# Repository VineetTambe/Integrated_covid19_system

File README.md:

# Integrated_covid19_system
Initially, a real-time camera feed is taken and the image-processing and detection using OpenCV.
1. The barcode is detected and decoded using a camera.    
2. The same camera is used to detect if the person is wearing a mask or not. This is done with the help of image processing and haar-cascade to give efficient and real-time output. The system also ensures whether a person is wearing a mask or not and it captures a photo and maintains a database of the violators.    
3. An infrared temperature sensor is then used to monitor the temperature of the person without any contact and maps it to the corresponding barcode which was read. The system also gives an alert when the temperature crosses a certain threshold.    

Further, all the data is stored in the cloud where the analysis of every individual is carried out to understand the temperature and other patterns.    

The unit also houses a touchless sanitizer dispenser which can be activated by hovering the hand below it.    

The dashboard application is a "one-stop-shop" for the management authorities to monitor the system and gain insight

[Click here for the demo](https://youtu.be/hhcx9HmFBgw)

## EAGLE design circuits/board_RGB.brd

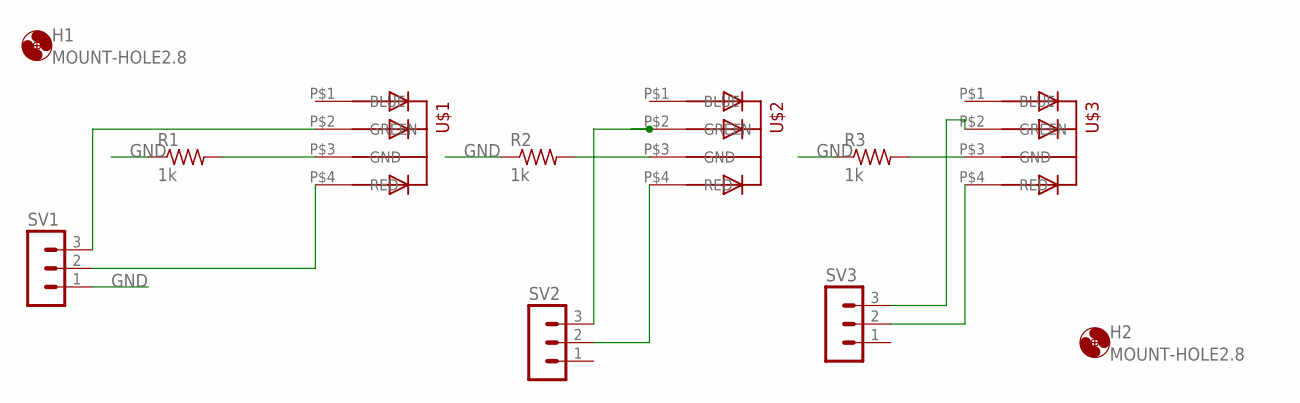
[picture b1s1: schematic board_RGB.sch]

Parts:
H1, H2: MOUNT-HOLE2.8; 2,8
R1, R2, R3: 1k; 0207/10
SV1, SV2, SV3: MA03-1
U$1, U$2, U$3: 5MMRGBLED; LED5MMRGB

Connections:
GND: R1.1, R2.1, R3.1, SV1.1
unnamed: SV2.2, U$2.P$4 (RED)
unnamed: R1.2, U$1.P$3 (GND)
unnamed: SV1.3, U$1.P$2 (GREEN)
unnamed: SV3.2, U$3.P$4 (RED)
unnamed: SV3.3, U$3.P$2 (GREEN)
unnamed: R3.2, U$3.P$3 (GND)
unnamed: R2.2, U$2.P$3 (GND)
unnamed: SV1.2, U$1.P$4 (RED)
unnamed: SV2.3, U$2.P$2 (GREEN)

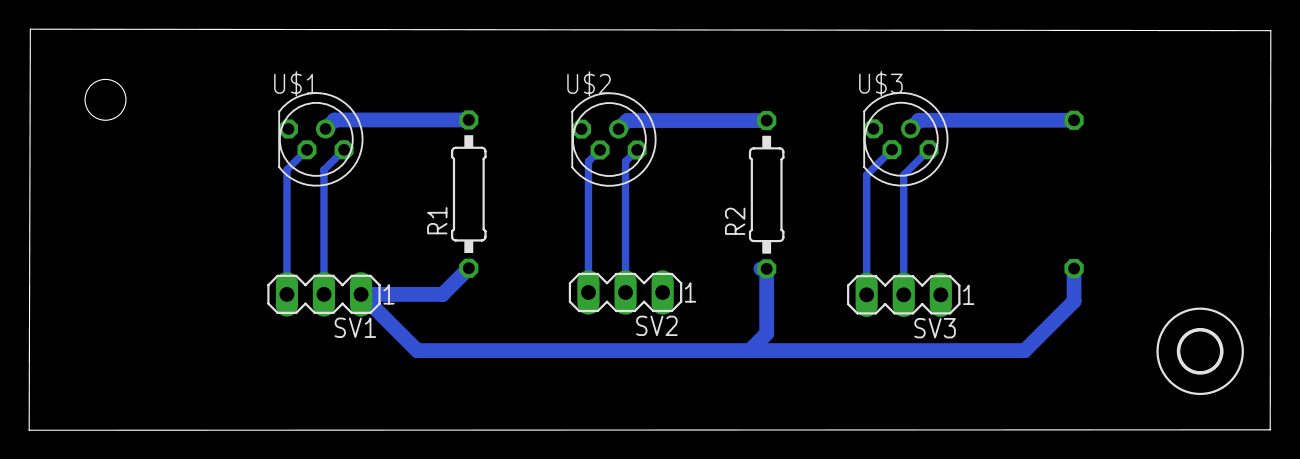
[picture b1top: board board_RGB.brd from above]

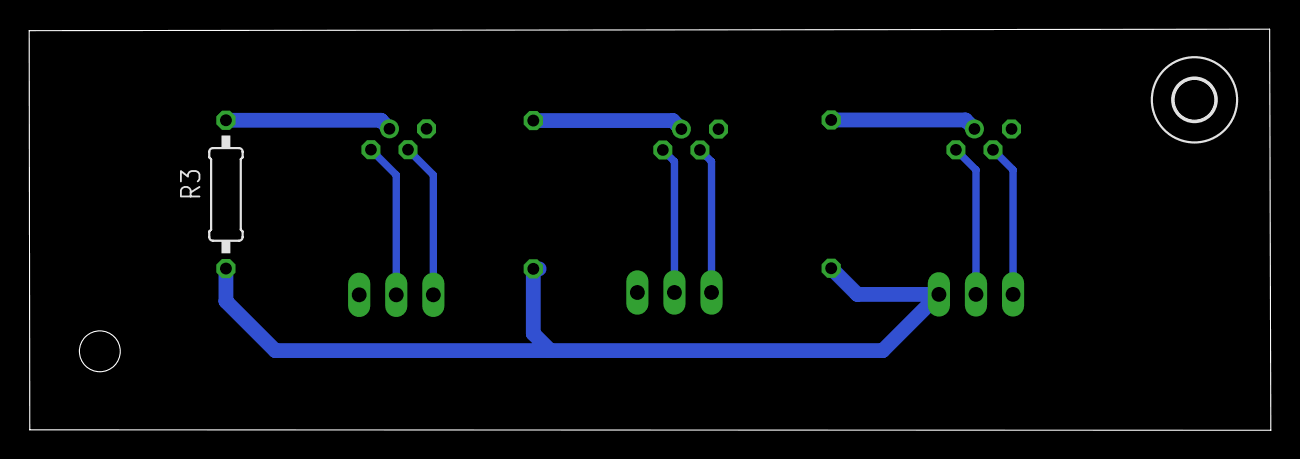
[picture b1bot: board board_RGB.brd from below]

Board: 2 copper layers, 85.1 x 27.5 mm, 11 parts (2 on the bottom side), 10 nets.

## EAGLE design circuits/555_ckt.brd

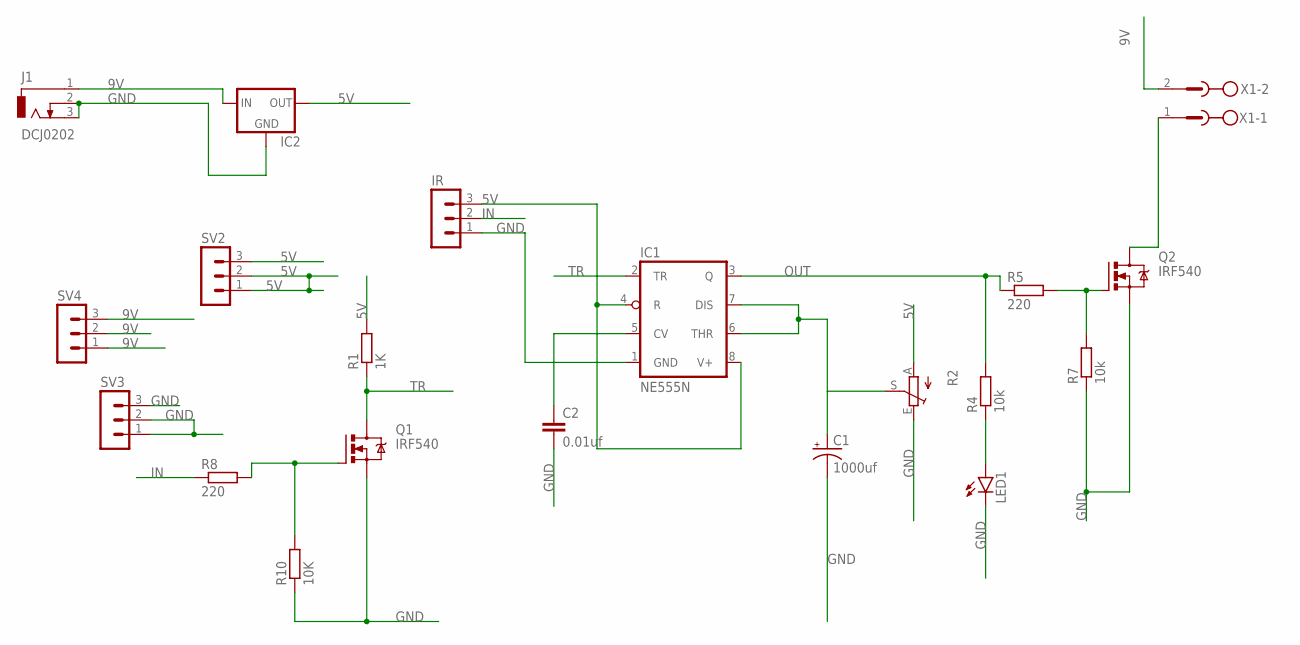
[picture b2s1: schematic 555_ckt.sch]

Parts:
C1: 1000uf; E2,5-7
C2: 0.01uf; C025-024X044
IC1: NE555N; DIL08
IC2: 78XXL
IR: MA03-1
J1: DCJ0202
LED1: LED3MM
Q1, Q2: IRF540; TO220BV
R1: 1K; 0207/10
R2: TRIM_EU-B64Y; B64Y
R4, R7: 10k; 0207/10
R5, R8: 220; 0207/10
R10: 10K; 0207/10
SV2, SV3, SV4: MA03-1
X1: MSTBV2

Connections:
5V: IC1.4 (R), IC1.8 (V+), IC2.OUT, IR.3, R1.2, R2.A, SV2.1, SV2.2, SV2.3
9V: IC2.IN, J1.1, SV4.1, SV4.2, SV4.3, X1.2
GND: C1.-, C2.2, IC1.1 (GND), IC2.GND, IR.1, J1.2, J1.3, LED1.K (C), Q1.S, Q2.S, R2.E, R7.1, R10.1, SV3.1, SV3.2, SV3.3
IN: IR.2, R8.1
unnamed: C2.1, IC1.5 (CV)
unnamed: Q1.G, R8.2, R10.2
unnamed: C1.+, IC1.6 (THR), IC1.7 (DIS), R2.S
unnamed: Q2.G, R5.2, R7.2
unnamed: LED1.A, R4.1
unnamed: Q2.D, X1.1
OUT: IC1.3 (Q), R4.2, R5.1
TR: IC1.2 (TR), Q1.D, R1.1

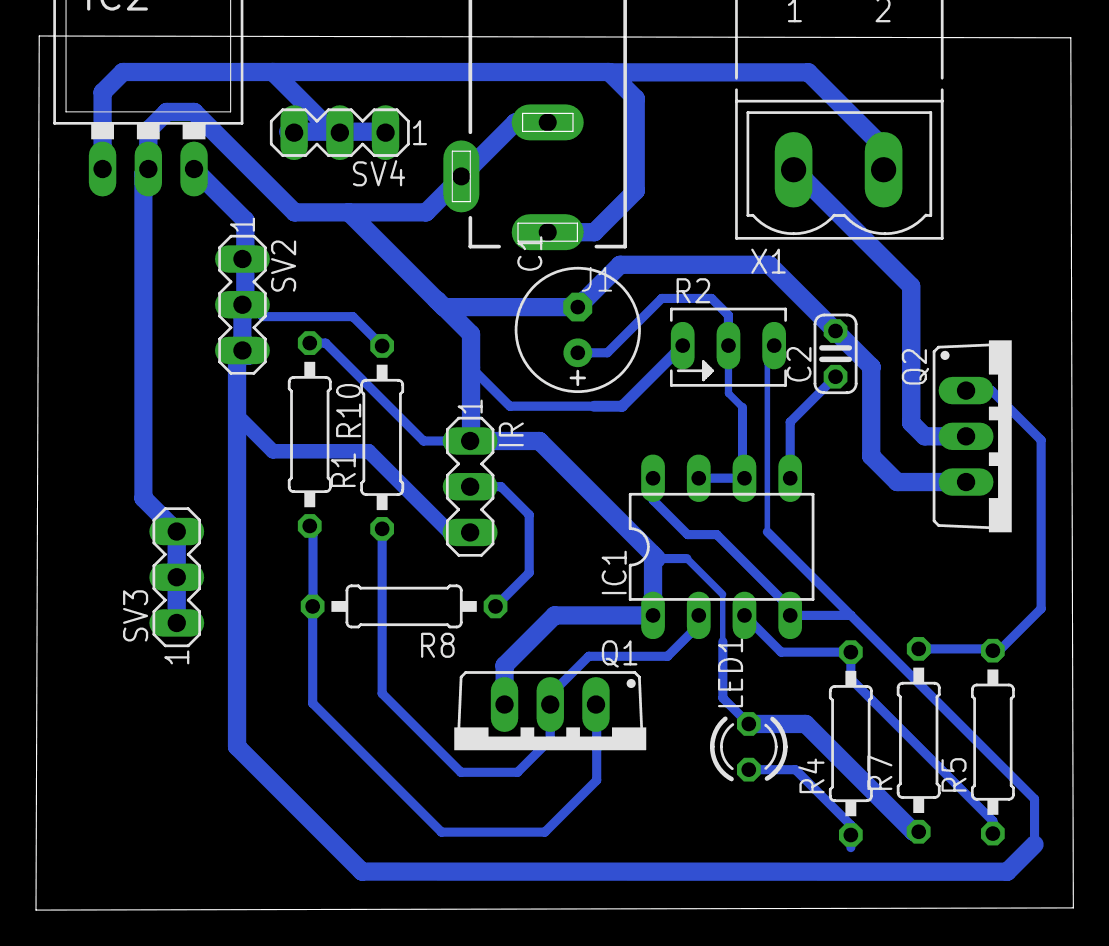
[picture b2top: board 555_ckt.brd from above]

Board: 2 copper layers, 57.6 x 48.6 mm, 20 parts (0 on the bottom side), 12 nets.

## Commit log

2020-07-25 added GPL liscence
2020-07-25 Updated code
2020-08-30 Add opencv code and files
2020-08-30 Add Final_integrate.py
2020-08-30 Add Arduino code and circuit files
2020-11-02 Update README.md
    add demo link
2020-11-09 add ultrasonic ode
2020-11-09 add firebase code
2020-11-25 add sanitzerdelay macro
2020-12-11 add youtube link
2020-12-21 commenting out buzzerPinb
2020-12-28 add integare3.py
2020-12-28 add integrate3-3.py
2020-12-29 add connections pdf
2020-12-29 add search_csv
2021-01-11 final integrate 3-3
2021-04-09 refactored and integrated led_buzzer.py
2021-04-09 modified lcdbuzzer to led_buzzer
2021-04-09 refactor complete
